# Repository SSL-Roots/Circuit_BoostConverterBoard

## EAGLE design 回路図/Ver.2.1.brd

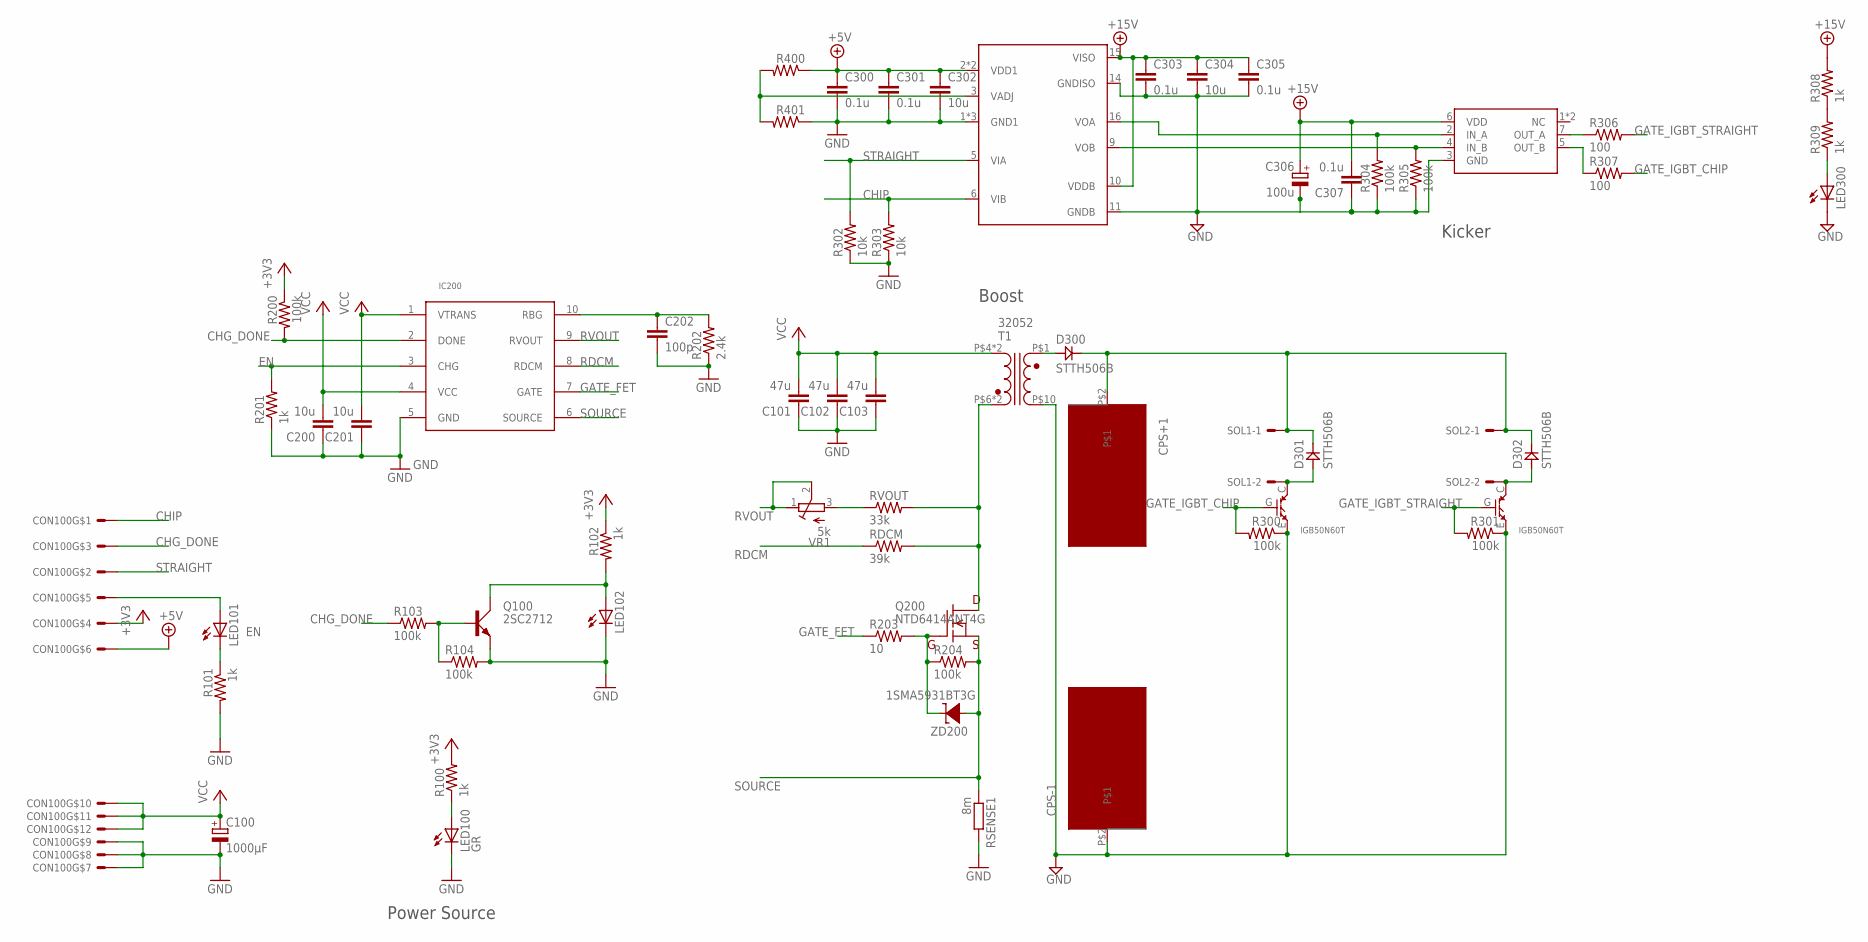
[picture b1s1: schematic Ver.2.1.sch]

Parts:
C100: 1000μF; E5-10
C101, C102, C103: 47u; C3216
C200, C201, C302, C304: 10u; C1608
C202: 100p; C5B5.5
C300, C301, C303, C305, C307: 0.1u; C1608
C306: 100u; E2,5-6
CON100: 12B-XH-AB12B; B12B-XH-A
CPS+1: POWER_SOURCE_PAD
CPS-1: POWER_SOURCE_PAD
D300, D301, D302: STTH506B; DPAK
IC200: LT3750; MSOP10
IC300: ADUM5230; SOIC-16
IC301: TC4427; SOIC-8
LED100: GR; LED3MM
LED101, LED102, LED300: LED3MM
Q100: 2SC2712; TO23
Q200: NTD6414ANT4G; TO-252
Q300, Q301: IGB50N60T; D2PACK
R100, R101, R102, R201, R308, R309: 1k; R1608
R103, R104, R200, R204, R300, R301, R304, R305: 100k; R1608
R202: 2.4k; 0204/5S
R203: 10; 0204/7
R302, R303: 10k; R1608
R306, R307: 100; R1608
R400, R401: R-US_R1608; R1608
RDCM: 39k; 0204/7
RSENSE1: 8m; M3216
RVOUT: 33k; 0204/7
SOL1, SOL2: KK-156-2-RA-NH; 22-05-3021-NH
T1: 32052
VR1: 5k; RTRIM64W_S
ZD200: 1SMA5931BT3G; DO214AC

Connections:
200: CPS+1.P$2, D300.K, D301.K, D302.K, SOL1.1, SOL2.1
+3V3: CON100.4, R100.2, R102.1, R200.1
+5V: C300.1, C301.1, C302.1, CON100.6, IC300.2 (VDD1), IC300.7 (VDD1), R400.1
+15V: C303.1, C304.1, C305.1, C306.+, C307.2, IC300.10 (VDDB), IC300.15 (VISO), IC301.6 (VDD), R308.2
CHG_DONE: CON100.3, IC200.2 (DONE), R103.1, R200.2
CHIP: CON100.1, IC300.6 (VIB), R303.2
C_GND: C303.2, C304.2, C305.2, C306.-, C307.1, CPS-1.P$2, IC300.11 (GNDB), IC300.14 (GNDISO), IC301.3 (GND), LED300.K (C), Q300.E, Q301.E, R300.1, R301.1, R304.1, R305.1, T1.P$10 (4)
EN: CON100.5, IC200.3 (CHG), LED101.A, R201.2
GATE_FET: IC200.7 (GATE), R203.1
GATE_IGBT_CHIP: Q300.G, R300.2, R307.2
GATE_IGBT_STRAIGHT: Q301.G, R301.2, R306.2
GND: C100.-, C101.1, C102.1, C103.1, C200.1, C201.1, C202.2, C300.2, C301.2, C302.2, CON100.7, CON100.8, CON100.9, IC200.5 (GND), IC300.1 (GND1), IC300.4 (GND1), IC300.8 (GND1), LED100.K (C), LED102.K (C), Q100.E, R101.2, R104.2, R201.1, R202.1, R302.1, R303.1, R401.1, RSENSE1.2
unnamed: LED100.A, R100.1
unnamed: Q200.D, RDCM.2, RVOUT.2, T1.P$6 (2), T1.P$7 (2)
unnamed: Q200.G, R203.2, R204.1, ZD200.C (K)
unnamed: RVOUT.1, VR1.3 (E)
unnamed: D300.A, T1.P$1 (3)
unnamed: D301.A, Q300.C, SOL1.2
unnamed: D302.A, Q301.C, SOL2.2
unnamed: Q100.B, R103.2, R104.1
unnamed: LED300.A, R309.1
unnamed: C202.1, IC200.10 (RBG), R202.2
unnamed: LED102.A, Q100.C, R102.2
unnamed: IC300.9 (VOB), IC301.4 (IN_B), R305.2
unnamed: IC300.16 (VOA), IC301.2 (IN_A), R304.2
unnamed: IC300.3 (VADJ), R400.2, R401.2
unnamed: R308.1, R309.2
unnamed: IC301.7 (OUT_A), R306.1
unnamed: IC301.5 (OUT_B), R307.1
unnamed: LED101.K (C), R101.1
RDCM: IC200.8 (RDCM), RDCM.1
RVOUT: IC200.9 (RVOUT), VR1.1 (A), VR1.2 (S)
SOURCE: IC200.6 (SOURCE), Q200.S, R204.2, RSENSE1.1, ZD200.A
STRAIGHT: CON100.2, IC300.5 (VIA), R302.2
VCC: C100.+, C101.2, C102.2, C103.2, C200.2, C201.2, CON100.10, CON100.11, CON100.12, IC200.1 (VTRANS), IC200.4 (VCC), T1.P$4 (1), T1.P$5 (1)

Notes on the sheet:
Power Source
Boost
Kicker

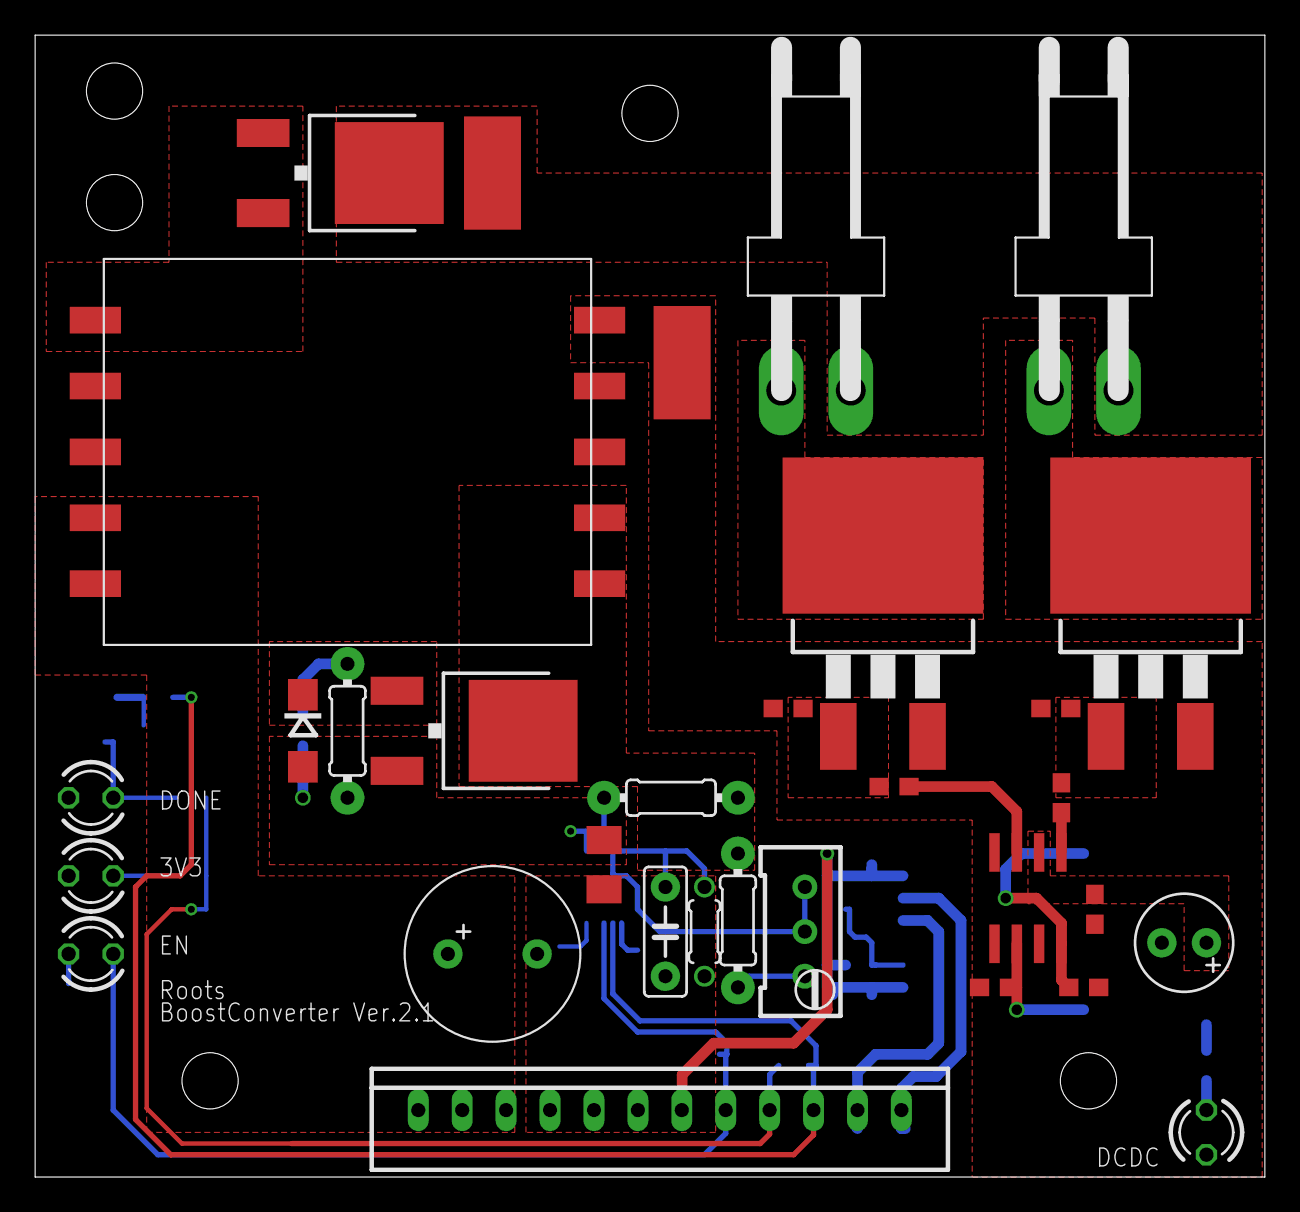
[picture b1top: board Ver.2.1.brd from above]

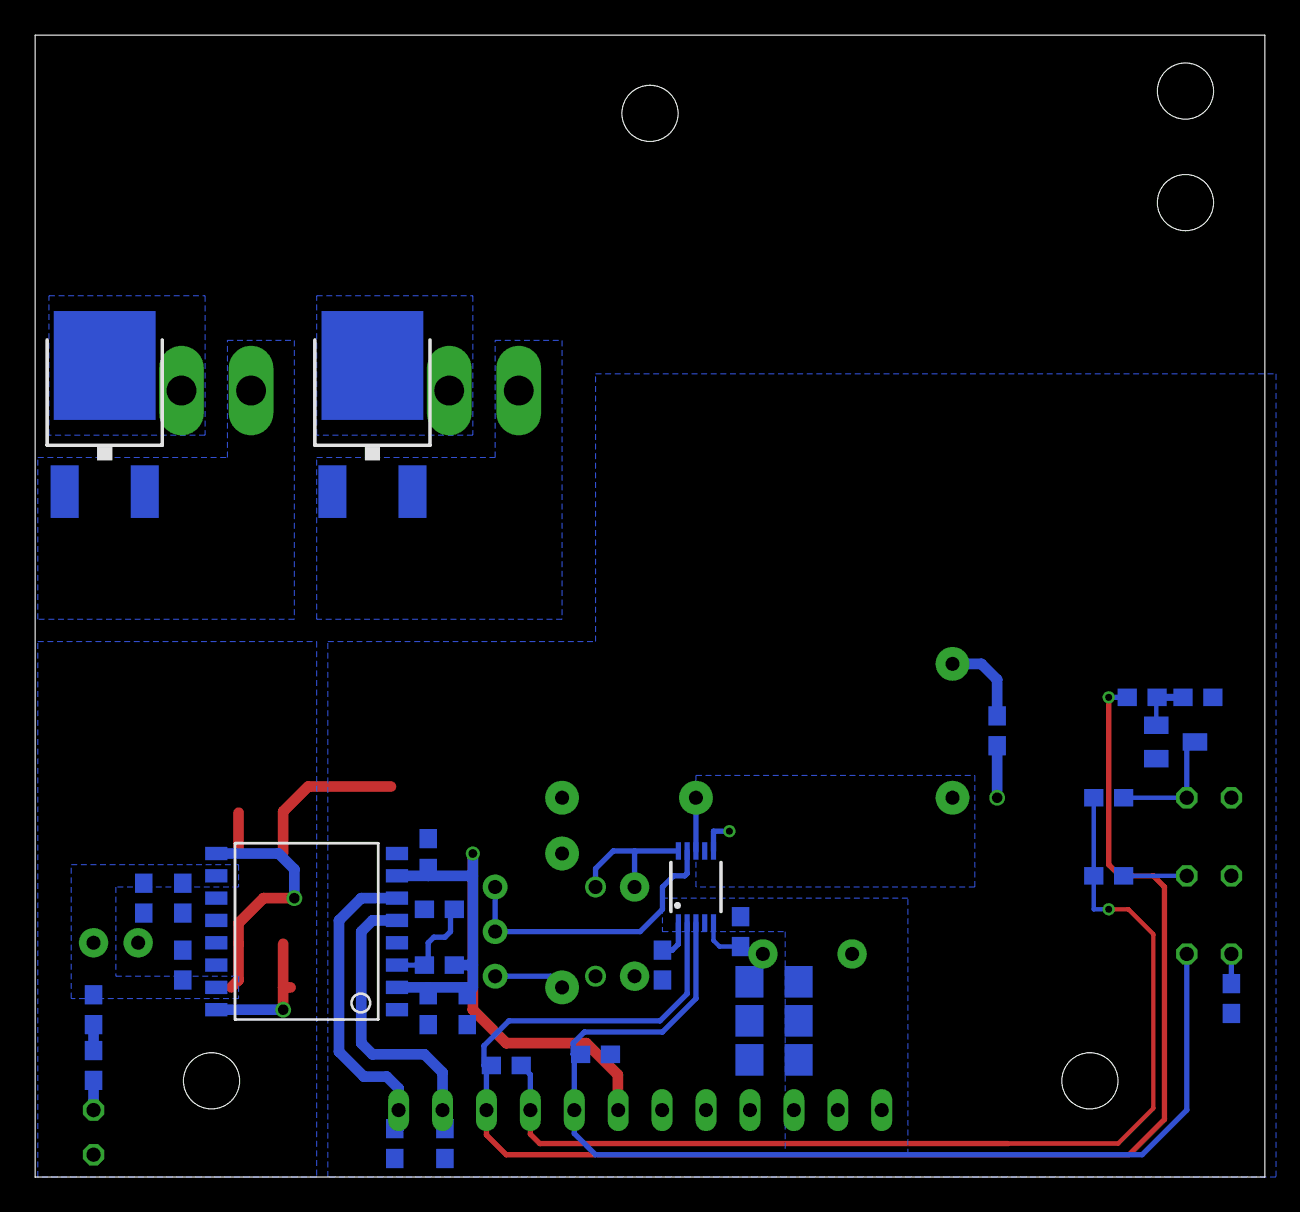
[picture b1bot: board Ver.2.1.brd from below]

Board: 2 copper layers, 70.0 x 65.0 mm, 62 parts (30 on the bottom side), 35 nets.
